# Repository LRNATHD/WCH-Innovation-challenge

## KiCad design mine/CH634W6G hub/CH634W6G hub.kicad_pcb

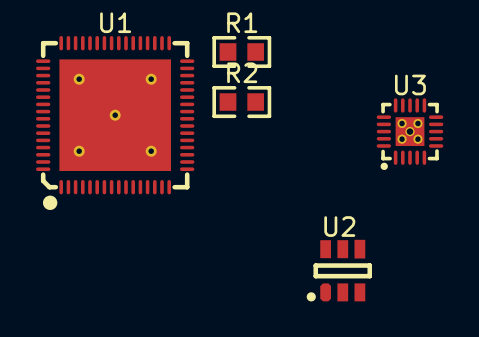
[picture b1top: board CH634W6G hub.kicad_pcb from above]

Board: 2 copper layers, 5 parts (0 on the bottom side), 4 nets, no tracks yet.

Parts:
R1: 24k; 0603
R2: 51k; 0603
U1: CH634W6G; QFN64_8X8
U2: *; SOT-23-6
U3: CH211D; QFN20_3X3

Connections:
/PWRSTART: U1.34 (PWREN#), U2.4 (EN#)
/PWRSTOP: R2.1, U1.33 (OVCUR#), U2.3 (FLAG#)
GND: R1.1, U2.2 (GND)
unnamed: R1.2, U2.5 (ISET)

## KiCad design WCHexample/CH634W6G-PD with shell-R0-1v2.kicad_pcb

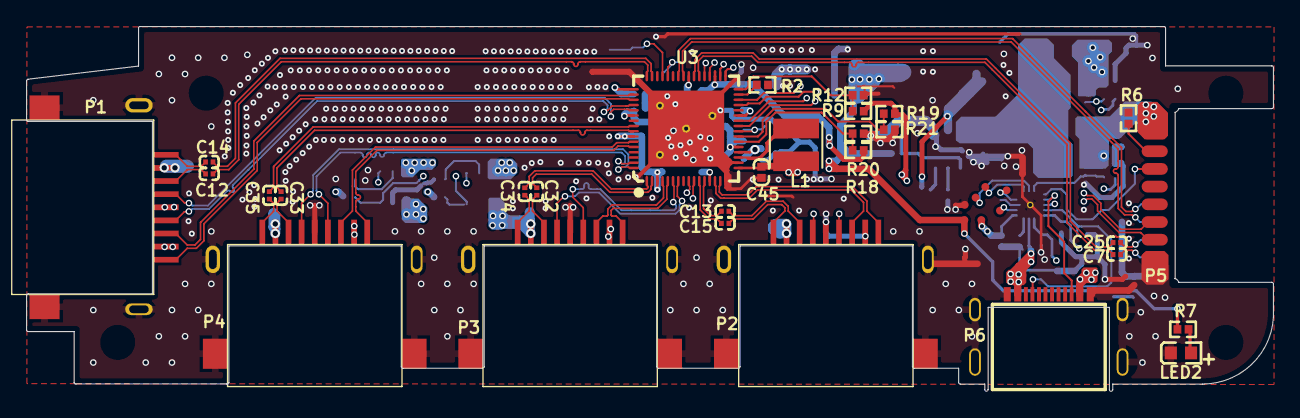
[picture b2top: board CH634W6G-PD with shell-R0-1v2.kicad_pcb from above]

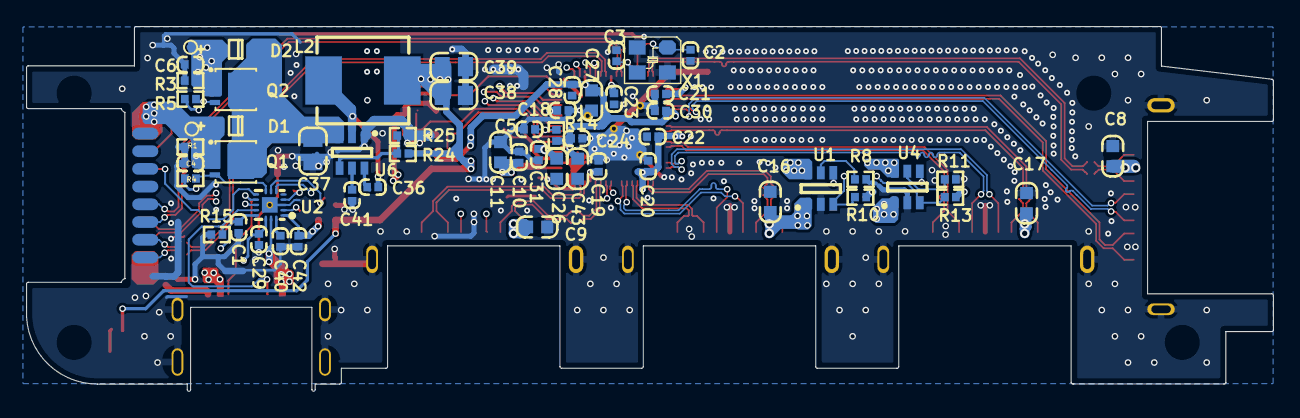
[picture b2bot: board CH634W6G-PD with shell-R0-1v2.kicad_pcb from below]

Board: 4 copper layers, 95.1 x 27.8 mm, 86 parts (58 on the bottom side), 77 nets.

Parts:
C1, C36: 100nF; 0402_C
C2, C3: 20pF; 0402_C
C4, C6, C10, C29, C31, C40, C41, C42: 1uF; 0402_C
C5: NC(0.1uF); 0402_C
C7, C12, C13, C14, C15, C25, C32, C33, C34, C35: 0.1uF; 0201_C
C8, C9, C11, C16, C17, C26, C27, C43: 10uF; 0603_C
C18, C19, C20, C21, C22, C23, C24, C28, C30, C45: 0.1uF; 0402_C
C37, C38, C39: 22uF; 0805_C
D1, D2: SS34; SOD-123
L1: 2.2uH; CD32
L2: 15uH; IND-SMD_L7.0-W6.6
LED2: 5V; 0603+
P1: PORT1; USB-3.0F-TL
P2: PORT2; USB-3.0F-TL
P3: PORT3; USB-3.0F-TL
P4: PORT4; USB-3.0F-TL
P5: UP; CABLE-TYPEC1
P6: TYPE-C; TYPE-C-Receptacle-2.0-16PIN-L6.5mmSinkDown1.2mm
Q1, Q2: SE3060D; DFN-8_L3.1-W3.0-P0.65-LS3.3-BL
R1, R2, R3, R18, R19: 10K; 0402
R4, R5: 680KΩ; 0402
R6: 1KΩ; 0402
R7: 2K; 0402
R8, R11: 24K; 0402
R9, R12, R20, R21: NC(10K); 0402
R10, R13: NC(51K); 0402
R14: 0Ω(10K); 0402
R15: 5.1KΩ; 0402
R24: 105K; 0402
R25: 20K; 0402
TP1, TP2: Testpoint; TESTPOINT3
U1, U4: CH217K; SOT-23-6
U2: CH211C; QFN16C_2X2
U3: CH634W6G; QFN64_8X8
U6: ETA2807; SOT-23-6
X1: 24MHz; XT3225

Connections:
AVDD33: C24.1, C27.1, C28.2, C30.2, C42.1, C43.1, R9.2, R10.1, R13.1, R14.2, R18.2, R19.2, U2.1, U3.21, U3.35, U3.54
CC1_P1: P6.A5, R15.1, U2.12
CC1_P2: P5.11, U2.9
CC2_P1: P6.B5, U2.10
CFG0: R18.1, R20.2, U3.22
CFG1: R19.1, R21.2, U3.23
GND: C1.1, C2.2, C3.1, C4.1, C5.1, C6.1, C8.2, C9.2, C10.1, C11.2, C16.2, C17.2, C18.1, C19.1, C20.1, C21.1, C22.1, C23.1, C24.2, C26.1, C27.2, C28.1, C29.2, C30.1, C31.1, C37.1, C38.1, C39.1, C40.2, C41.1, C42.2, C43.2, C45.1, LED2.2, P1.0, P1.4, P1.7, P2.0, P2.4, P2.7, P3.0, P3.4, P3.7, P4.0, P4.4, P4.7, P5.16, P6.0, P6.A1, P6.A12, P6.B1, P6.B12, R1.2, R2.1, R3.2, R6.2, R8.2, R11.2, R12.1, R15.2, R20.1, R21.1, R25.1, U1.2, U2.0, U2.3, U3.0, U3.16, U3.18, U4.2, U6.1, X1.2, X1.4
HVCP: C1.2, R4.2, R5.2, U2.13
NetC7_2: C7.2, P5.7
NetC12_1: C12.1, P1.8
NetC13_1: C13.1, P2.8
NetC14_1: C14.1, P1.9
NetC15_1: C15.1, P2.9
NetC25_2: C25.2, P5.8
NetC32_1: C32.1, P3.8
NetC33_1: C33.1, P4.8
NetC34_1: C34.1, P3.9
NetC35_1: C35.1, P4.9
NetC36_1: C36.1, L2.1, U6.2
NetC36_2: C36.2, U6.6
NetC40_1: C40.1, U2.16
NetC41_2: C41.2, U6.5
NetLED2_1: LED2.1, R7.1
NetP5_10: P5.10, R6.1
NetR8_1: R8.1, U1.5
NetR11_1: R11.1, U4.5
NetR24_1: R24.1, R25.2, U6.4
OVCUR#: R10.2, R13.2, U1.3, U3.33, U4.3
P1_HS_DM: P1.2, U3.53
P1_HS_DP: P1.3, U3.52
P1_SS_RXA: P1.5, U3.51
P1_SS_RXB: P1.6, U3.50
P1_SS_TXA: C12.2, U3.48
P1_SS_TXB: C14.2, U3.47
P2_HS_DM: P2.2, U3.10
P2_HS_DP: P2.3, U3.9
P2_SS_RXA: P2.5, U3.15
P2_SS_RXB: P2.6, U3.14
P2_SS_TXA: C13.2, U3.12
P2_SS_TXB: C15.2, U3.11
P3_HS_DM: P3.2, U3.7
P3_HS_DP: P3.3, U3.6
P3_SS_RXA: P3.5, U3.5
P3_SS_RXB: P3.6, U3.4
P3_SS_TXA: C32.2, U3.2
P3_SS_TXB: C34.2, U3.1
P4_HS_DM: P4.2, U3.64
P4_HS_DP: P4.3, U3.63
P4_SS_RXA: P4.5, U3.60
P4_SS_RXB: P4.6, U3.59
P4_SS_TXA: C33.2, U3.57
P4_SS_TXB: C35.2, U3.56
PDHUB#: R2.2, U3.31
PWREN#: U1.4, U3.34, U4.4
RESET#: C5.2, R14.1, U3.24
RSVD/HUB_CC: U2.7, U3.26
SPI_MISO/SDA: U2.2, U3.30
SPI_SCK/SCL: U2.4, U3.29
SUSP/CFG2: R9.1, R12.2, U3.32
UP_HS_DM: P5.14, U3.36
UP_HS_DP: P5.15, U3.37
UP_SS_RXA: P5.5, U3.42
UP_SS_RXB: P5.6, U3.41
UP_SS_TXA: C7.1, U3.39
UP_SS_TXB: C25.1, U3.38
VBUS: C4.2, C29.1, D1.1, P5.9, Q1.1, Q1.2, Q1.3, R1.1, TP1.1, U2.14
VBUS_DET/PWR_CC: U2.6, U3.25
VBUS_EN: Q1.4, R4.1, U2.8
VBUS_OUT: C8.1, C9.1, C16.1, C17.1, P1.1, P2.1, P3.1, P4.1, U1.1, U4.1
VDD5: C26.2, C31.2, C38.2, C39.2, L2.2, R7.2, R24.2, U1.6, U3.20, U4.6
VFB: C10.2, C11.1, C18.2, C19.2, C20.2, C21.2, C22.2, C23.2, C45.2, L1.2, U3.3, U3.13, U3.17, U3.27, U3.40, U3.49, U3.58
VHV: C37.2, D1.2, D2.2, Q1.5, Q1.6, Q1.7, Q1.8, Q2.5, Q2.6, Q2.7, Q2.8, U6.3
VIN: C6.2, D2.1, P6.A4, P6.A9, P6.B4, P6.B9, Q2.1, Q2.2, Q2.3, R3.1, TP2.1, U2.15
VIN_EN: Q2.4, R5.1, U2.11
VSW: L1.1, U3.19
XI: C2.1, U3.45, X1.1
XO: C3.2, U3.44, X1.3

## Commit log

2025-10-21 started work
2025-10-22 got the protection in?
2025-10-23 got a bit more pins labeled
2025-10-28 why am I even redesigning the schematic, im just gonna use example, this is a backup
